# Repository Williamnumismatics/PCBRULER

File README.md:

# PCBRULER
 THis is my first project in blueprint it is just a simple ruler
 
 I made it because i have always wanted a good ruler. I think it is also a good place to put references for smd sizes and like calculations. I also want to give one to one of my close friends as a birthday gift.
 
 Firstly I didnt touch the shematic because i didnt need to then i created the edge cuts and added the cm and mm lines. there is one line per mm and one larger line each 5mm there is a bigger line at 1cm. Then i added a quote that i liked which was "Measure twice, Panic once" i also added footprints on the left for me to esaily use when i am designing a pcb next time. I also added the first 100 digits of pi to the right side cause realistically i didnt know what to put there. 
 
 On the underside, I put my github link and my name and year i created this and also useful formulas and conversions to easily see when doing electronic projects in the future. Then i added a nutritional guideline table because i thought it was funny :) I also added a second QR code which leads to rick roll :)) All in all this is a very useful ruler for me as lots of my references are on here in one thing that i can easily carry around. 
 
On the top side, there is a 30cm ruler and some useful things those useful things include smd references, and for fun the first 100 digits of pi. THe underside has a qr code to my github and also some useful formulas.

### Update
The reviewer has said that i have to add some more usefulness to my ruler so i am going to add a rp2040 board and cascillated holes as pins. I am going to build in some rgbs, a oled and some bottons to chose which program to run. I might add a battery to it. So far i have done most of the schematic for the rp2040

### Bill of Materials (BOM)

| Item | Quantity | URL | Price (USD) |
|------|---------|-----|-------------|
| PCB | 5 | [Link](https://cart.jlcpcb.com/quote?orderType=1&homeUploadNum=6f552ba165f94ad8b5276539fe3203e9&businessType=example&fileName=PCB.zipA) | 9.81 |

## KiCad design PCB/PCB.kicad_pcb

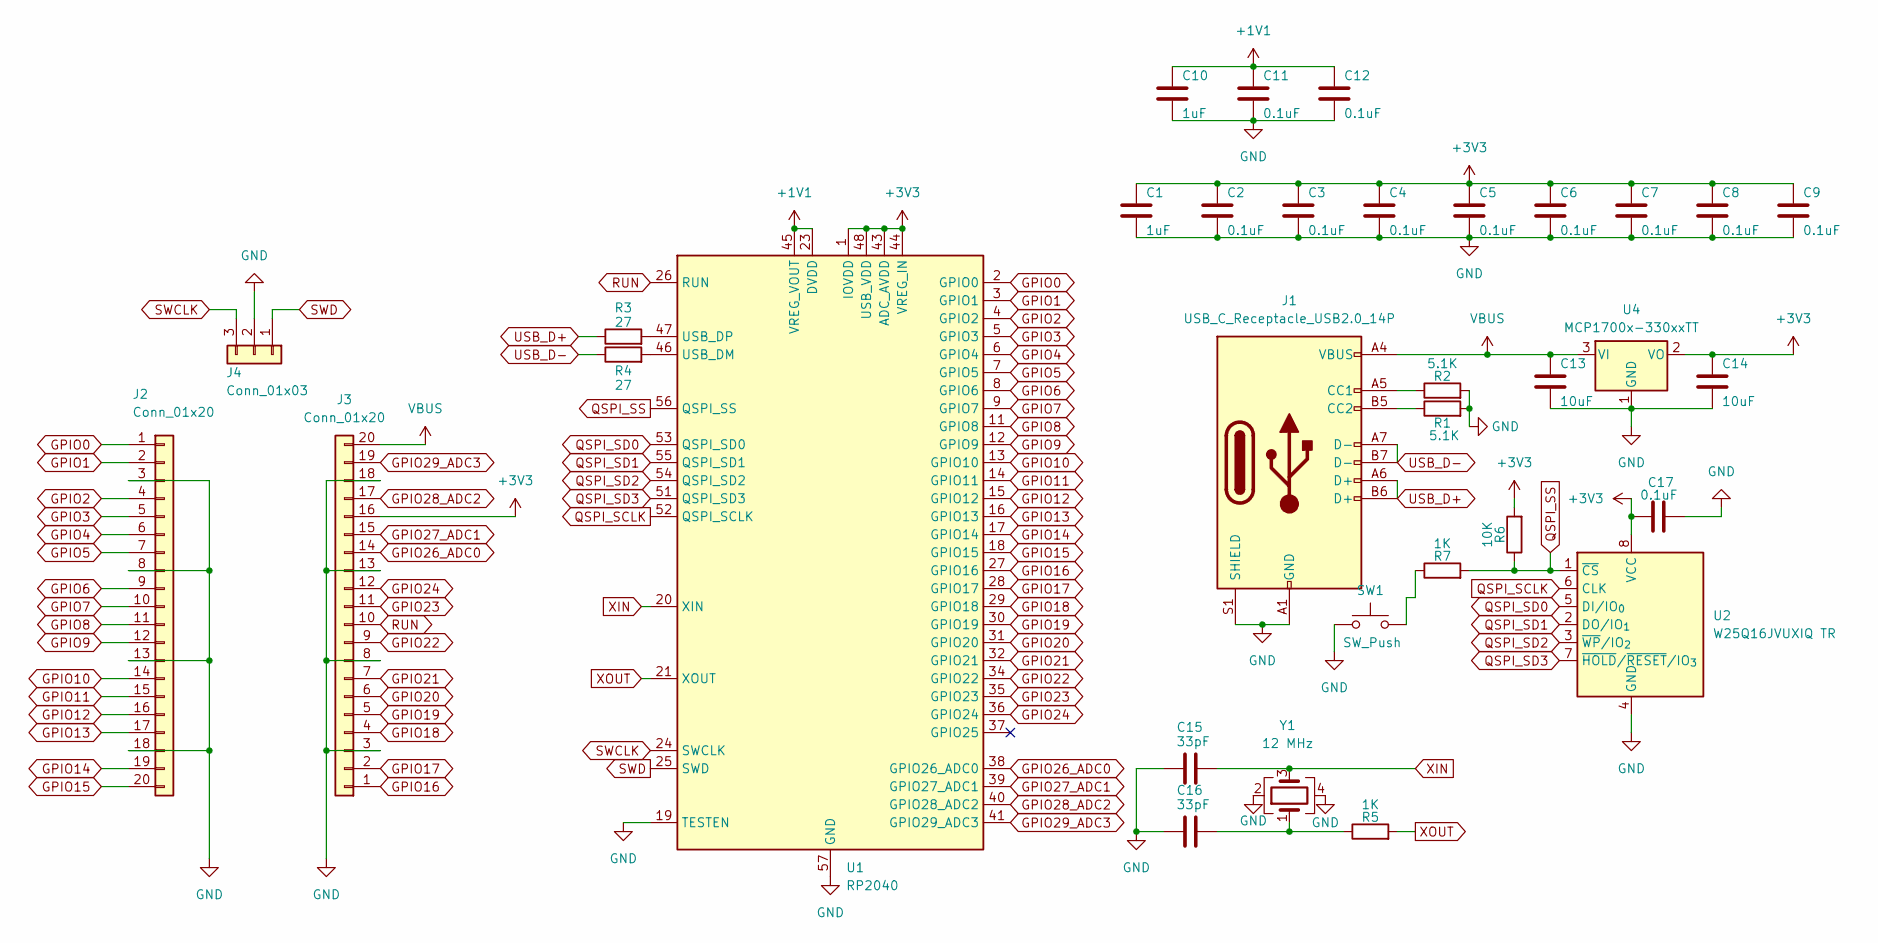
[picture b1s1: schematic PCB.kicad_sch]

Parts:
C1, C10: 1uF; C_0402_1005Metric
C2, C3, C4, C5, C6, C7, C8, C9, C11, C12, C17: 0.1uF; C_0402_1005Metric
C13, C14: 10uF; C_0402_1005Metric
C15, C16: 33pF; C_0402_1005Metric
J1: USB_C_Receptacle_USB2.0_14P; USB_C_Receptacle_HRO_TYPE-C-31-M-12
J2, J3: Conn_01x20; 20_SMD
J4: Conn_01x03; 3_SMD
R1, R2: 5.1K; R_0402_1005Metric
R3, R4: 27; R_0402_1005Metric
R5, R7: 1K; R_0402_1005Metric
R6: 10K; R_0402_1005Metric
SW1: SW_Push; SW_Push_SPST_NO_Alps_SKRK
U1: RP2040; QFN-56-1EP_7x7mm_P0.4mm_EP3.2x3.2mm
U2: W25Q16JVUXIQ TR; Winbond_USON-8-1EP_3x2mm_P0.5mm_EP0.2x1.6mm
U4: MCP1700x-330xxTT; SOT-23
Y1: 12 MHz; Crystal_SMD_3225-4Pin_3.2x2.5mm

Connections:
+1V1: C10.1, C11.1, C12.1, U1.23 (DVDD), U1.45 (VREG_VOUT), U1.50 (DVDD)
+3V3: C1.1, C2.1, C3.1, C4.1, C5.1, C6.1, C7.1, C8.1, C9.1, C14.1, C17.1, J3.16, R6.2, U1.1 (IOVDD), U1.10 (IOVDD), U1.22 (IOVDD), U1.33 (IOVDD), U1.42 (IOVDD), U1.43 (ADC_AVDD), U1.44 (VREG_IN), U1.48 (USB_VDD), U1.49 (IOVDD), U2.8 (VCC), U4.2 (VO)
GND: C1.2, C2.2, C3.2, C4.2, C5.2, C6.2, C7.2, C8.2, C9.2, C10.2, C11.2, C12.2, C13.2, C14.2, C15.1, C16.1, C17.2, J1.A1 (GND), J1.A12 (GND), J1.B1 (GND), J1.B12 (GND), J1.S1 (SHIELD), J2.3, J2.8, J2.13, J2.18, J3.3, J3.8, J3.13, J3.18, J4.2, R1.2, R2.2, SW1.1, U1.19 (TESTEN), U1.57 (GND), U2.4 (GND), U4.1 (GND), Y1.2, Y1.4
GPIO0: J2.1, U1.2 (GPIO0)
GPIO1: J2.2, U1.3 (GPIO1)
GPIO2: J2.4, U1.4 (GPIO2)
GPIO3: J2.5, U1.5 (GPIO3)
GPIO4: J2.6, U1.6 (GPIO4)
GPIO5: J2.7, U1.7 (GPIO5)
GPIO6: J2.9, U1.8 (GPIO6)
GPIO7: J2.10, U1.9 (GPIO7)
GPIO8: J2.11, U1.11 (GPIO8)
GPIO9: J2.12, U1.12 (GPIO9)
GPIO10: J2.14, U1.13 (GPIO10)
GPIO11: J2.15, U1.14 (GPIO11)
GPIO12: J2.16, U1.15 (GPIO12)
GPIO13: J2.17, U1.16 (GPIO13)
GPIO14: J2.19, U1.17 (GPIO14)
GPIO15: J2.20, U1.18 (GPIO15)
GPIO16: J3.1, U1.27 (GPIO16)
GPIO17: J3.2, U1.28 (GPIO17)
GPIO18: J3.4, U1.29 (GPIO18)
GPIO19: J3.5, U1.30 (GPIO19)
GPIO20: J3.6, U1.31 (GPIO20)
GPIO21: J3.7, U1.32 (GPIO21)
GPIO22: J3.9, U1.34 (GPIO22)
GPIO23: J3.11, U1.35 (GPIO23)
GPIO24: J3.12, U1.36 (GPIO24)
GPIO26_ADC0: J3.14, U1.38 (GPIO26_ADC0)
GPIO27_ADC1: J3.15, U1.39 (GPIO27_ADC1)
GPIO28_ADC2: J3.17, U1.40 (GPIO28_ADC2)
GPIO29_ADC3: J3.19, U1.41 (GPIO29_ADC3)
unnamed: C16.2, R5.1, Y1.1
unnamed: J1.A5 (CC1), R2.1
unnamed: J1.B5 (CC2), R1.1
unnamed: R7.1, SW1.2
unnamed: R4.2, U1.46 (USB_DM)
unnamed: R3.2, U1.47 (USB_DP)
QSPI_SCLK: U1.52 (QSPI_SCLK), U2.6 (CLK)
QSPI_SD0: U1.53 (QSPI_SD0), U2.5 (DI/IO_{0})
QSPI_SD1: U1.55 (QSPI_SD1), U2.2 (DO/IO_{1})
QSPI_SD2: U1.54 (QSPI_SD2), U2.3 (~WP/IO_{2})
QSPI_SD3: U1.51 (QSPI_SD3), U2.7 (~HOLD/~RESET/IO_{3})
QSPI_SS: R6.1, R7.2, U1.56 (QSPI_SS), U2.1 (~CS)
RUN: J3.10, U1.26 (RUN)
SWCLK: J4.3, U1.24 (SWCLK)
SWD: J4.1, U1.25 (SWD)
USB_D+: J1.A6 (D+), J1.B6 (D+), R3.1
USB_D-: J1.A7 (D-), J1.B7 (D-), R4.1
VBUS: C13.1, J1.A4 (VBUS), J1.A9 (VBUS), J1.B4 (VBUS), J1.B9 (VBUS), J3.20, U4.3 (VI)
XIN: C15.2, U1.20 (XIN), Y1.3
XOUT: R5.2, U1.21 (XOUT)

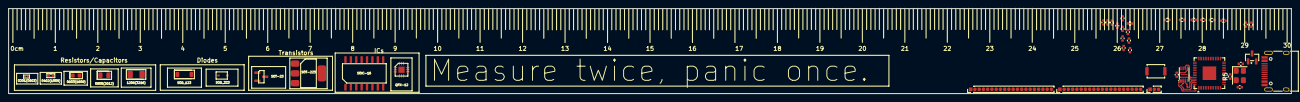
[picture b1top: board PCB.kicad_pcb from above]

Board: 2 copper layers, 302.0 x 20.0 mm, 33 parts (0 on the bottom side), 52 nets.

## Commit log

2025-10-25 added
2025-10-25 added more to the readme
2025-10-26 asdfa
2025-10-27 STuff
2025-10-27 more
